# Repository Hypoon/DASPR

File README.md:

Directory Descriptions:
* 2012 - latest EAGLE project files, including schematics, boards, and libraries.
* datasheets - datasheets for all external components used in the project.

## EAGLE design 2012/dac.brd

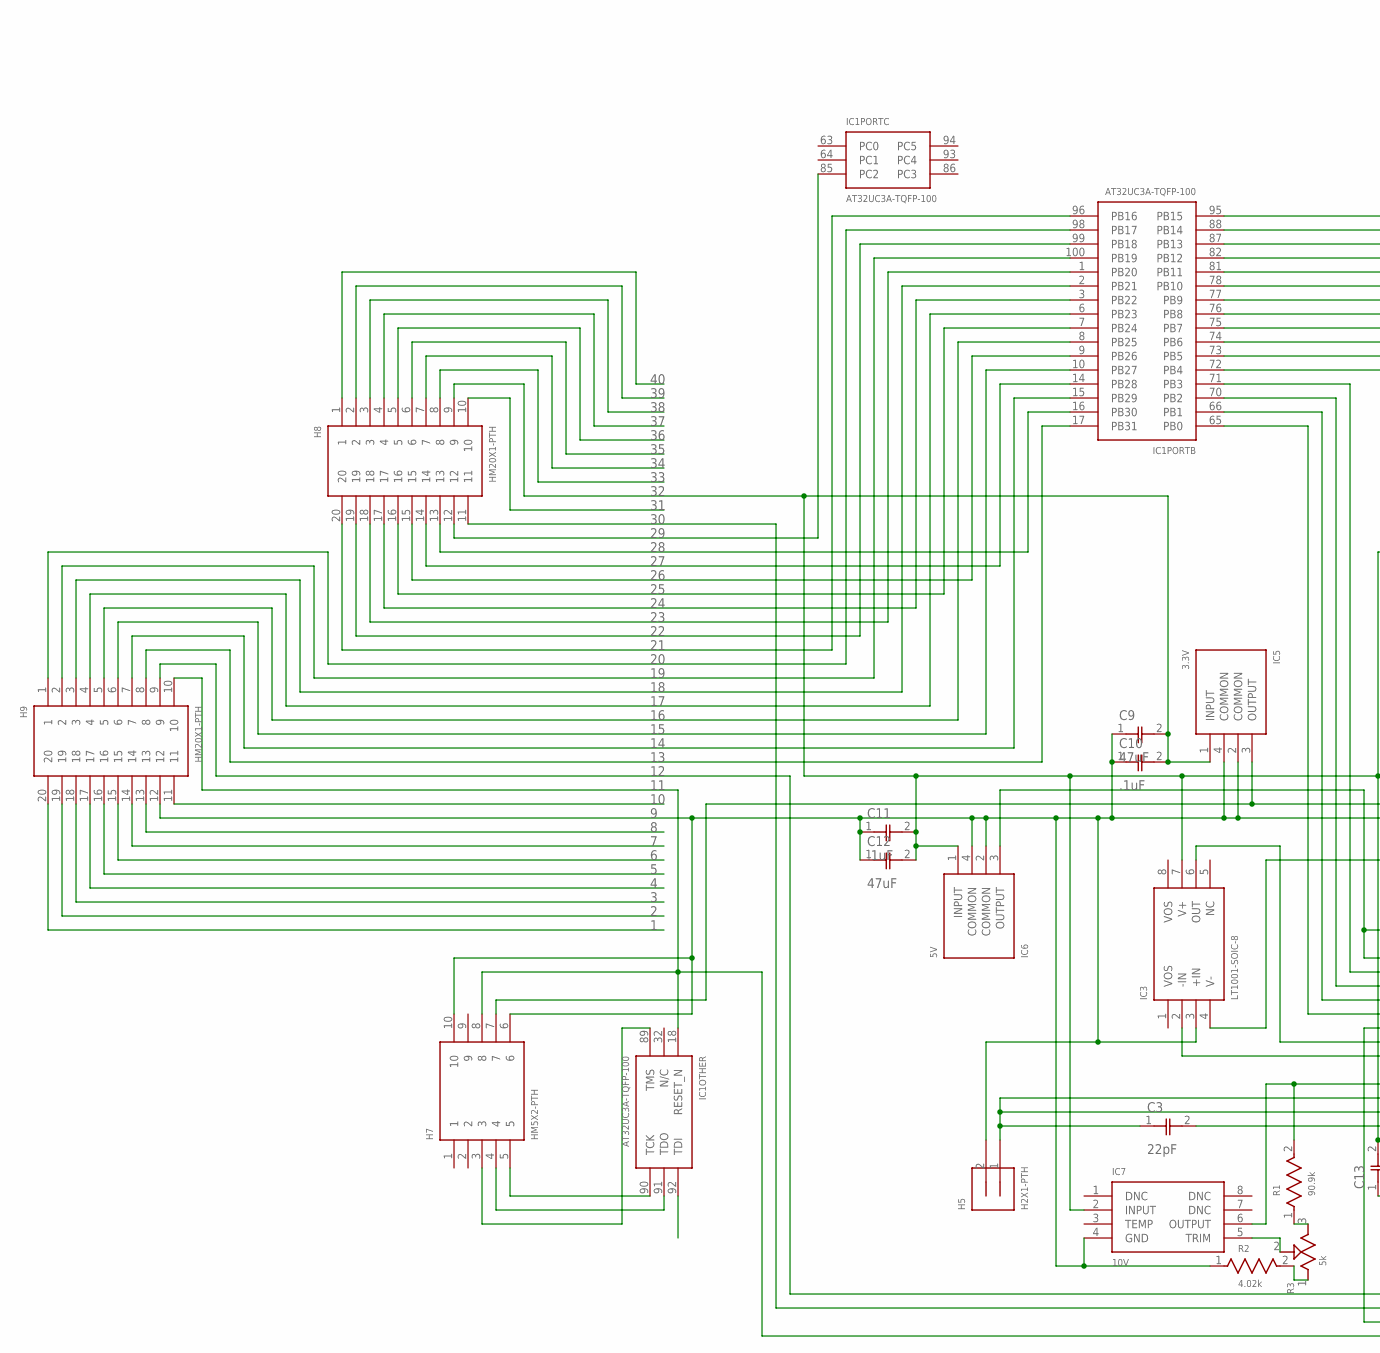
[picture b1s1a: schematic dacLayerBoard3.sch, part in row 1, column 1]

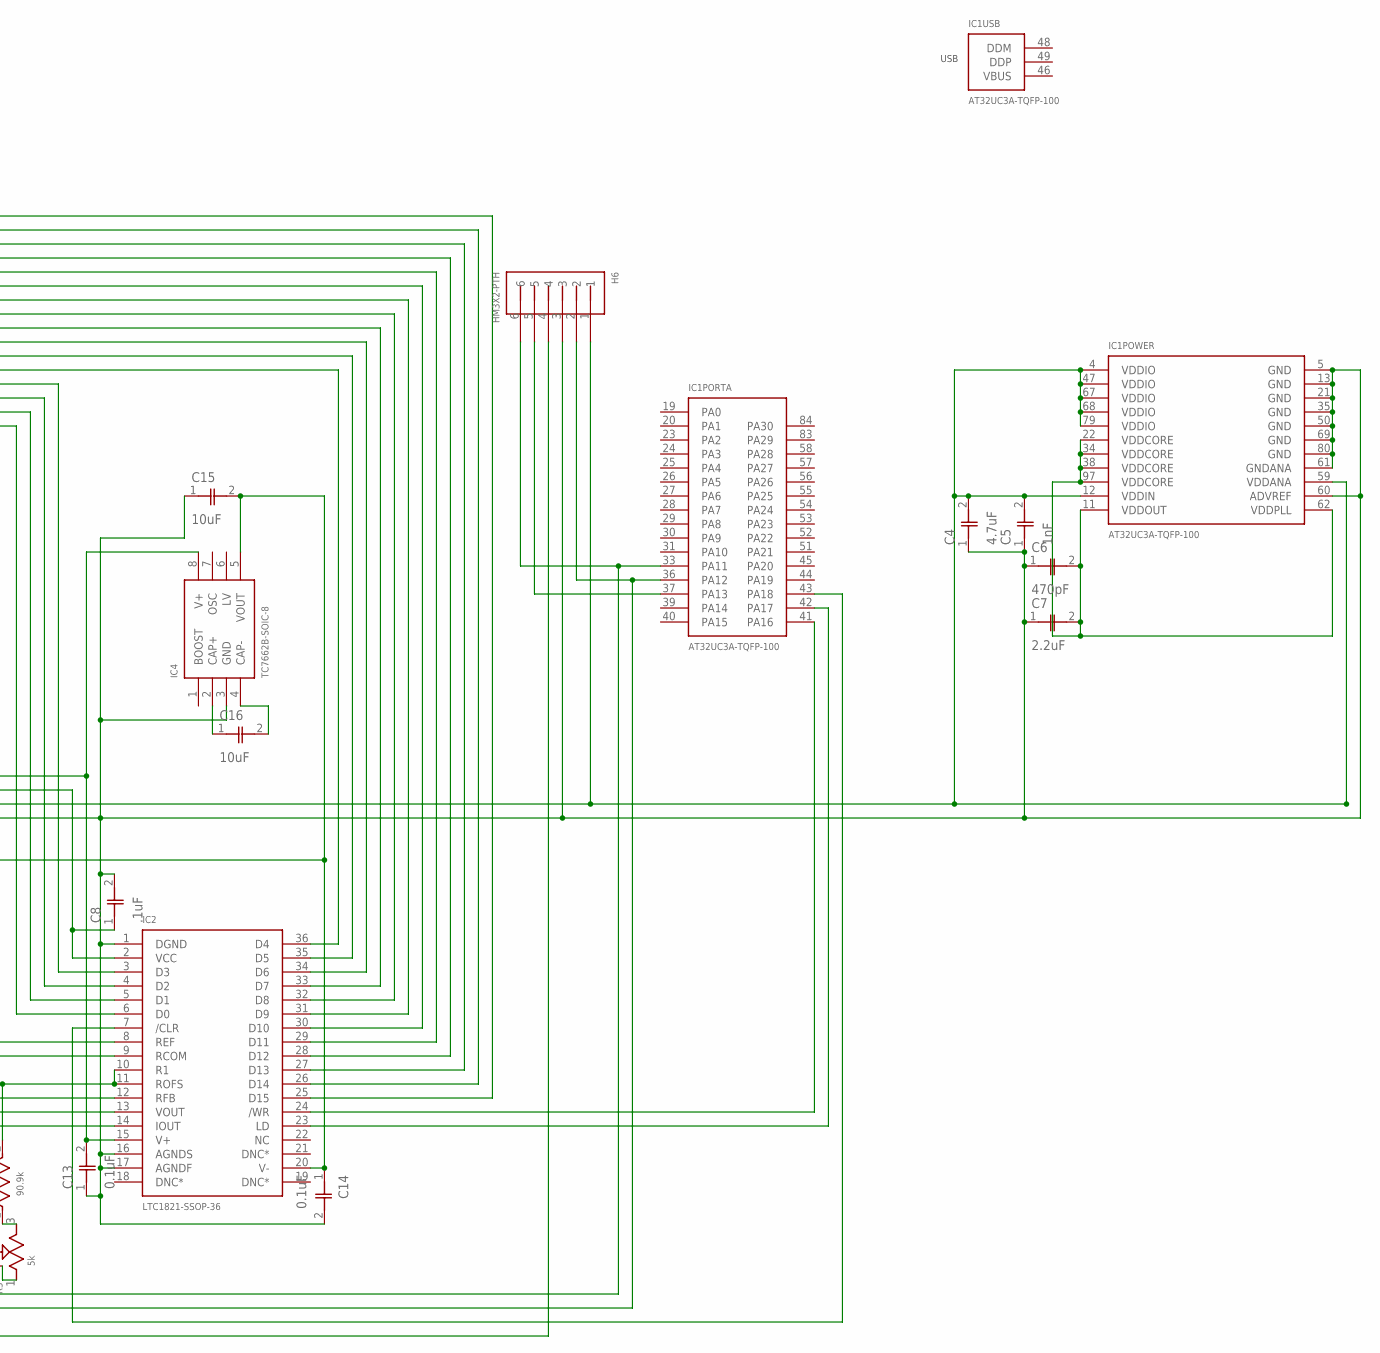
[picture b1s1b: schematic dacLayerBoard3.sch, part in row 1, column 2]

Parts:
C3: 22pF; CAP-0603
C4: 4.7uF; CAP-0603
C5: 1nF; CAP-0603
C6: 470pF; CAP-0603
C7: 2.2uF; CAP-0603
C8, C10, C11: .1uF; CAP-0603
C9, C12: 47uF; CAP-0603
C13, C14: 0.1uF; CAP-0603
C15, C16: 10uF; 0805
H5: H2X1-PTH; HM2X1-PTH
H6: HM3X2-PTH
H7: HM5X2-PTH
H8, H9: HM20X1-PTH
IC1: AT32UC3A-TQFP-100; TQFP-100
IC2: LTC1821-SSOP-36; SSOP-36
IC3: LT1001-SOIC-8; SOIC-8
IC4: TC7662B-SOIC-8; SOIC-8
IC5: 3.3V; SOT-223-4
IC6: 5V; SOT-223-4
IC7: 10V; SOIC-8
R1: 90.9k; RES-0603
R2: 4.02k; RES-0603
R3: 5k; 3303W

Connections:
1: H9.20
2: H9.19
3: H9.18
4: H9.17
5: H9.16
6: H9.15
7: H9.14
8: H9.13
9: C4.1, C5.1, C6.1, C7.1, C8.2, C9.1, C10.1, C11.1, C12.1, C13.1, C14.2, C15.1, H5.2, H6.3, H7.6, H7.10, H9.12, IC1.5 (GND), IC1.13 (GND), IC1.21 (GND), IC1.35 (GND), IC1.50 (GND), IC1.60 (ADVREF), IC1.61 (GNDANA), IC1.69 (GND), IC1.80 (GND), IC2.1 (DGND), IC2.16 (AGNDS), IC2.17 (AGNDF), IC3.3 (+IN), IC4.3 (GND), IC5.2 (COMMON), IC5.4 (COMMON), IC6.2 (COMMON), IC6.4 (COMMON), IC7.4 (GND), R2.1
10: H9.11
11: H6.4, H7.8, H9.10, IC1.18 (RESET_N)
12: H6.6, H9.9, IC1.33 (PA11)
13: H9.8, IC1.17 (PB31)
14: H9.7, IC1.15 (PB29)
15: H9.6, IC1.10 (PB27)
16: H9.5, IC1.8 (PB25)
17: H9.4, IC1.6 (PB23)
18: H9.3, IC1.2 (PB21)
19: H9.2, IC1.100 (PB19)
20: H9.1, IC1.98 (PB17)
21: H8.20, IC1.96 (PB16)
22: H8.19, IC1.99 (PB18)
23: H8.18, IC1.1 (PB20)
24: H8.17, IC1.3 (PB22)
25: H8.16, IC1.7 (PB24)
26: H8.15, IC1.9 (PB26)
27: H8.14, IC1.14 (PB28)
28: H8.13, IC1.16 (PB30)
29: H8.12, IC1.85 (PC2)
30: H6.2, H8.11, IC1.36 (PA12)
31: H8.10
32: C9.2, C10.2, C11.2, C12.2, C13.2, H8.9, IC2.15 (V+), IC3.7 (V+), IC4.8 (V+), IC5.1 (INPUT), IC6.1 (INPUT), IC7.2 (INPUT)
33: H8.8
34: H8.7
35: H8.6
36: H8.5
37: H8.4
38: H8.3
39: H8.2
40: H8.1
unnamed: IC2.9 (RCOM), IC3.2 (-IN)
unnamed: C8.1, IC2.2 (VCC), IC6.3 (OUTPUT)
unnamed: IC2.8 (REF), IC3.6 (OUT)
unnamed: C3.1, H5.1, IC2.12 (RFB), IC2.13 (VOUT)
unnamed: C3.2, IC2.14 (IOUT)
unnamed: C16.1, IC4.2 (CAP+)
unnamed: C16.2, IC4.4 (CAP-)
unnamed: C4.2, C5.2, H6.1, H7.7, IC1.4 (VDDIO), IC1.12 (VDDIN), IC1.47 (VDDIO), IC1.59 (VDDANA), IC1.67 (VDDIO), IC1.68 (VDDIO), IC1.79 (VDDIO), IC5.3 (OUTPUT)
unnamed: C6.2, C7.2, IC1.11 (VDDOUT), IC1.22 (VDDCORE), IC1.34 (VDDCORE), IC1.38 (VDDCORE), IC1.62 (VDDPLL), IC1.97 (VDDCORE)
unnamed: C14.1, C15.2, IC2.20 (V-), IC3.4 (V-), IC4.5 (VOUT)
unnamed: IC1.65 (PB0), IC2.6 (D0)
unnamed: IC1.66 (PB1), IC2.5 (D1)
unnamed: IC1.70 (PB2), IC2.4 (D2)
unnamed: IC1.71 (PB3), IC2.3 (D3)
unnamed: IC1.72 (PB4), IC2.36 (D4)
unnamed: IC1.73 (PB5), IC2.35 (D5)
unnamed: IC1.74 (PB6), IC2.34 (D6)
unnamed: IC1.75 (PB7), IC2.33 (D7)
unnamed: IC1.76 (PB8), IC2.32 (D8)
unnamed: IC1.77 (PB9), IC2.31 (D9)
unnamed: IC1.78 (PB10), IC2.30 (D10)
unnamed: IC1.81 (PB11), IC2.29 (D11)
unnamed: IC1.82 (PB12), IC2.28 (D12)
unnamed: IC1.87 (PB13), IC2.27 (D13)
unnamed: IC1.88 (PB14), IC2.26 (D14)
unnamed: IC1.95 (PB15), IC2.25 (D15)
unnamed: IC1.41 (PA16), IC2.24 (/WR)
unnamed: IC1.42 (PA17), IC2.23 (LD)
unnamed: IC1.43 (PA18), IC2.7 (/CLR)
unnamed: IC2.10 (R1), IC2.11 (ROFS), IC7.6 (OUTPUT), R1.2
unnamed: IC7.5 (TRIM), R3.2
unnamed: R1.1, R3.3
unnamed: R2.2, R3.1
unnamed: H7.5, IC1.90 (TCK)
unnamed: H7.4, IC1.91 (TDO)
unnamed: H7.3, IC1.89 (TMS)
unnamed: H6.5, IC1.37 (PA13)

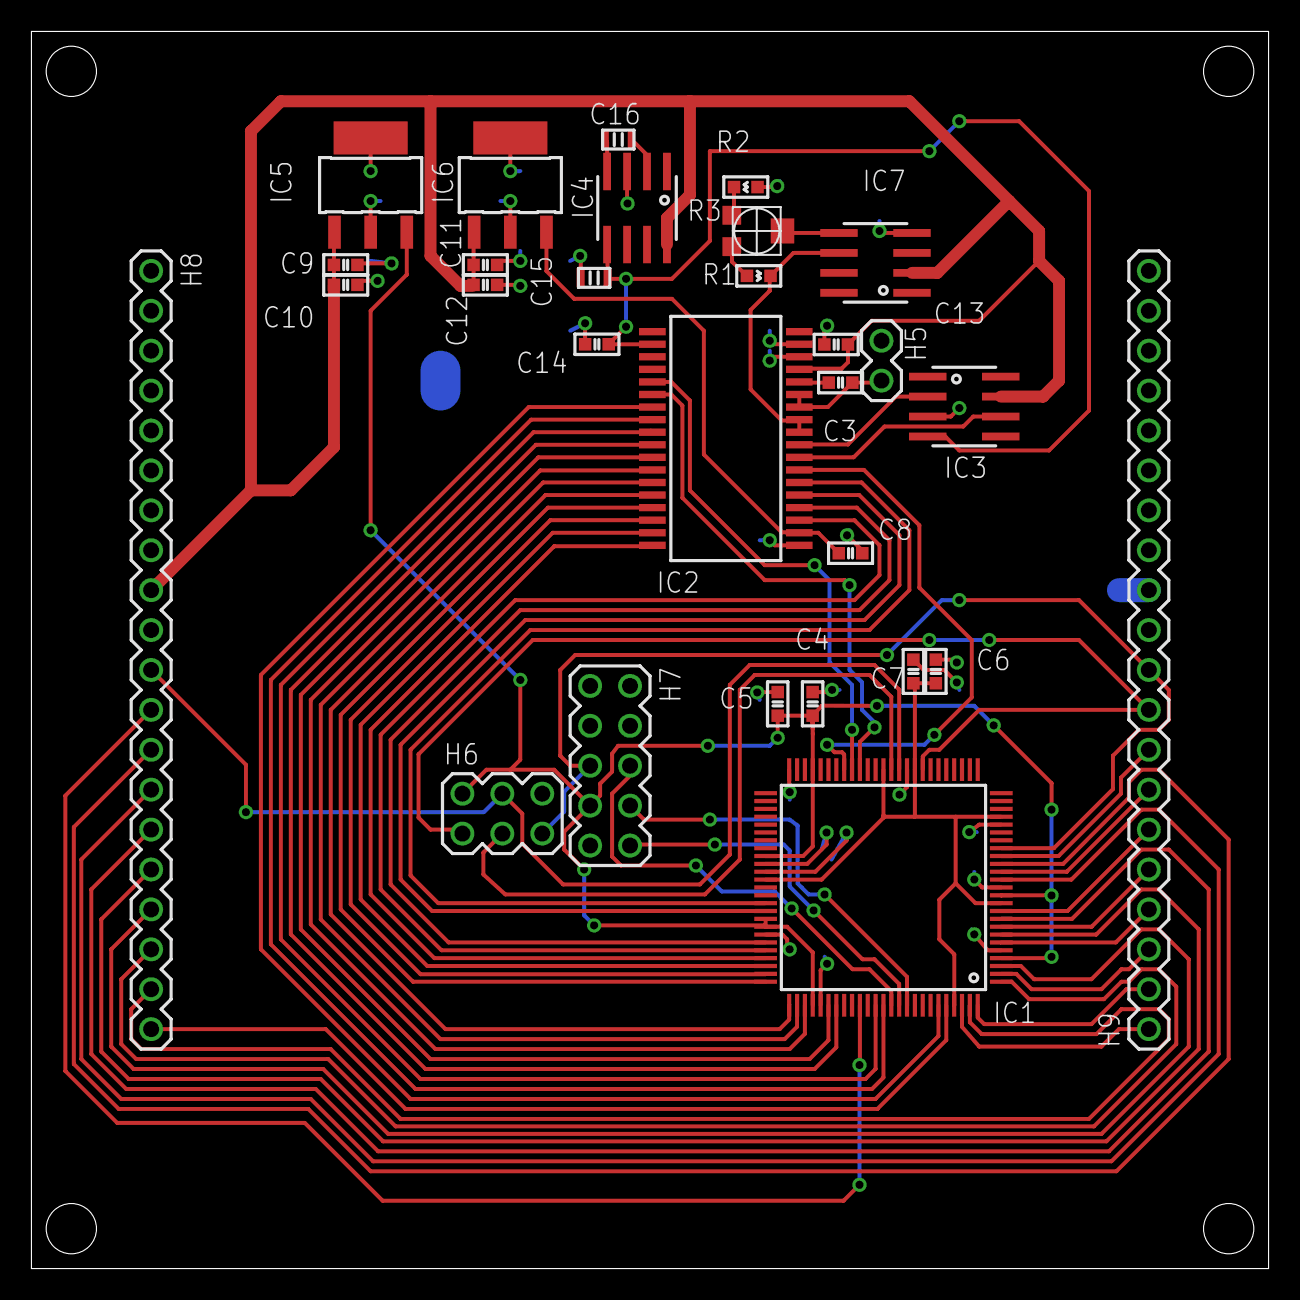
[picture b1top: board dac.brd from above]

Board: 2 copper layers, 78.7 x 78.7 mm, 29 parts (0 on the bottom side), 59 nets.

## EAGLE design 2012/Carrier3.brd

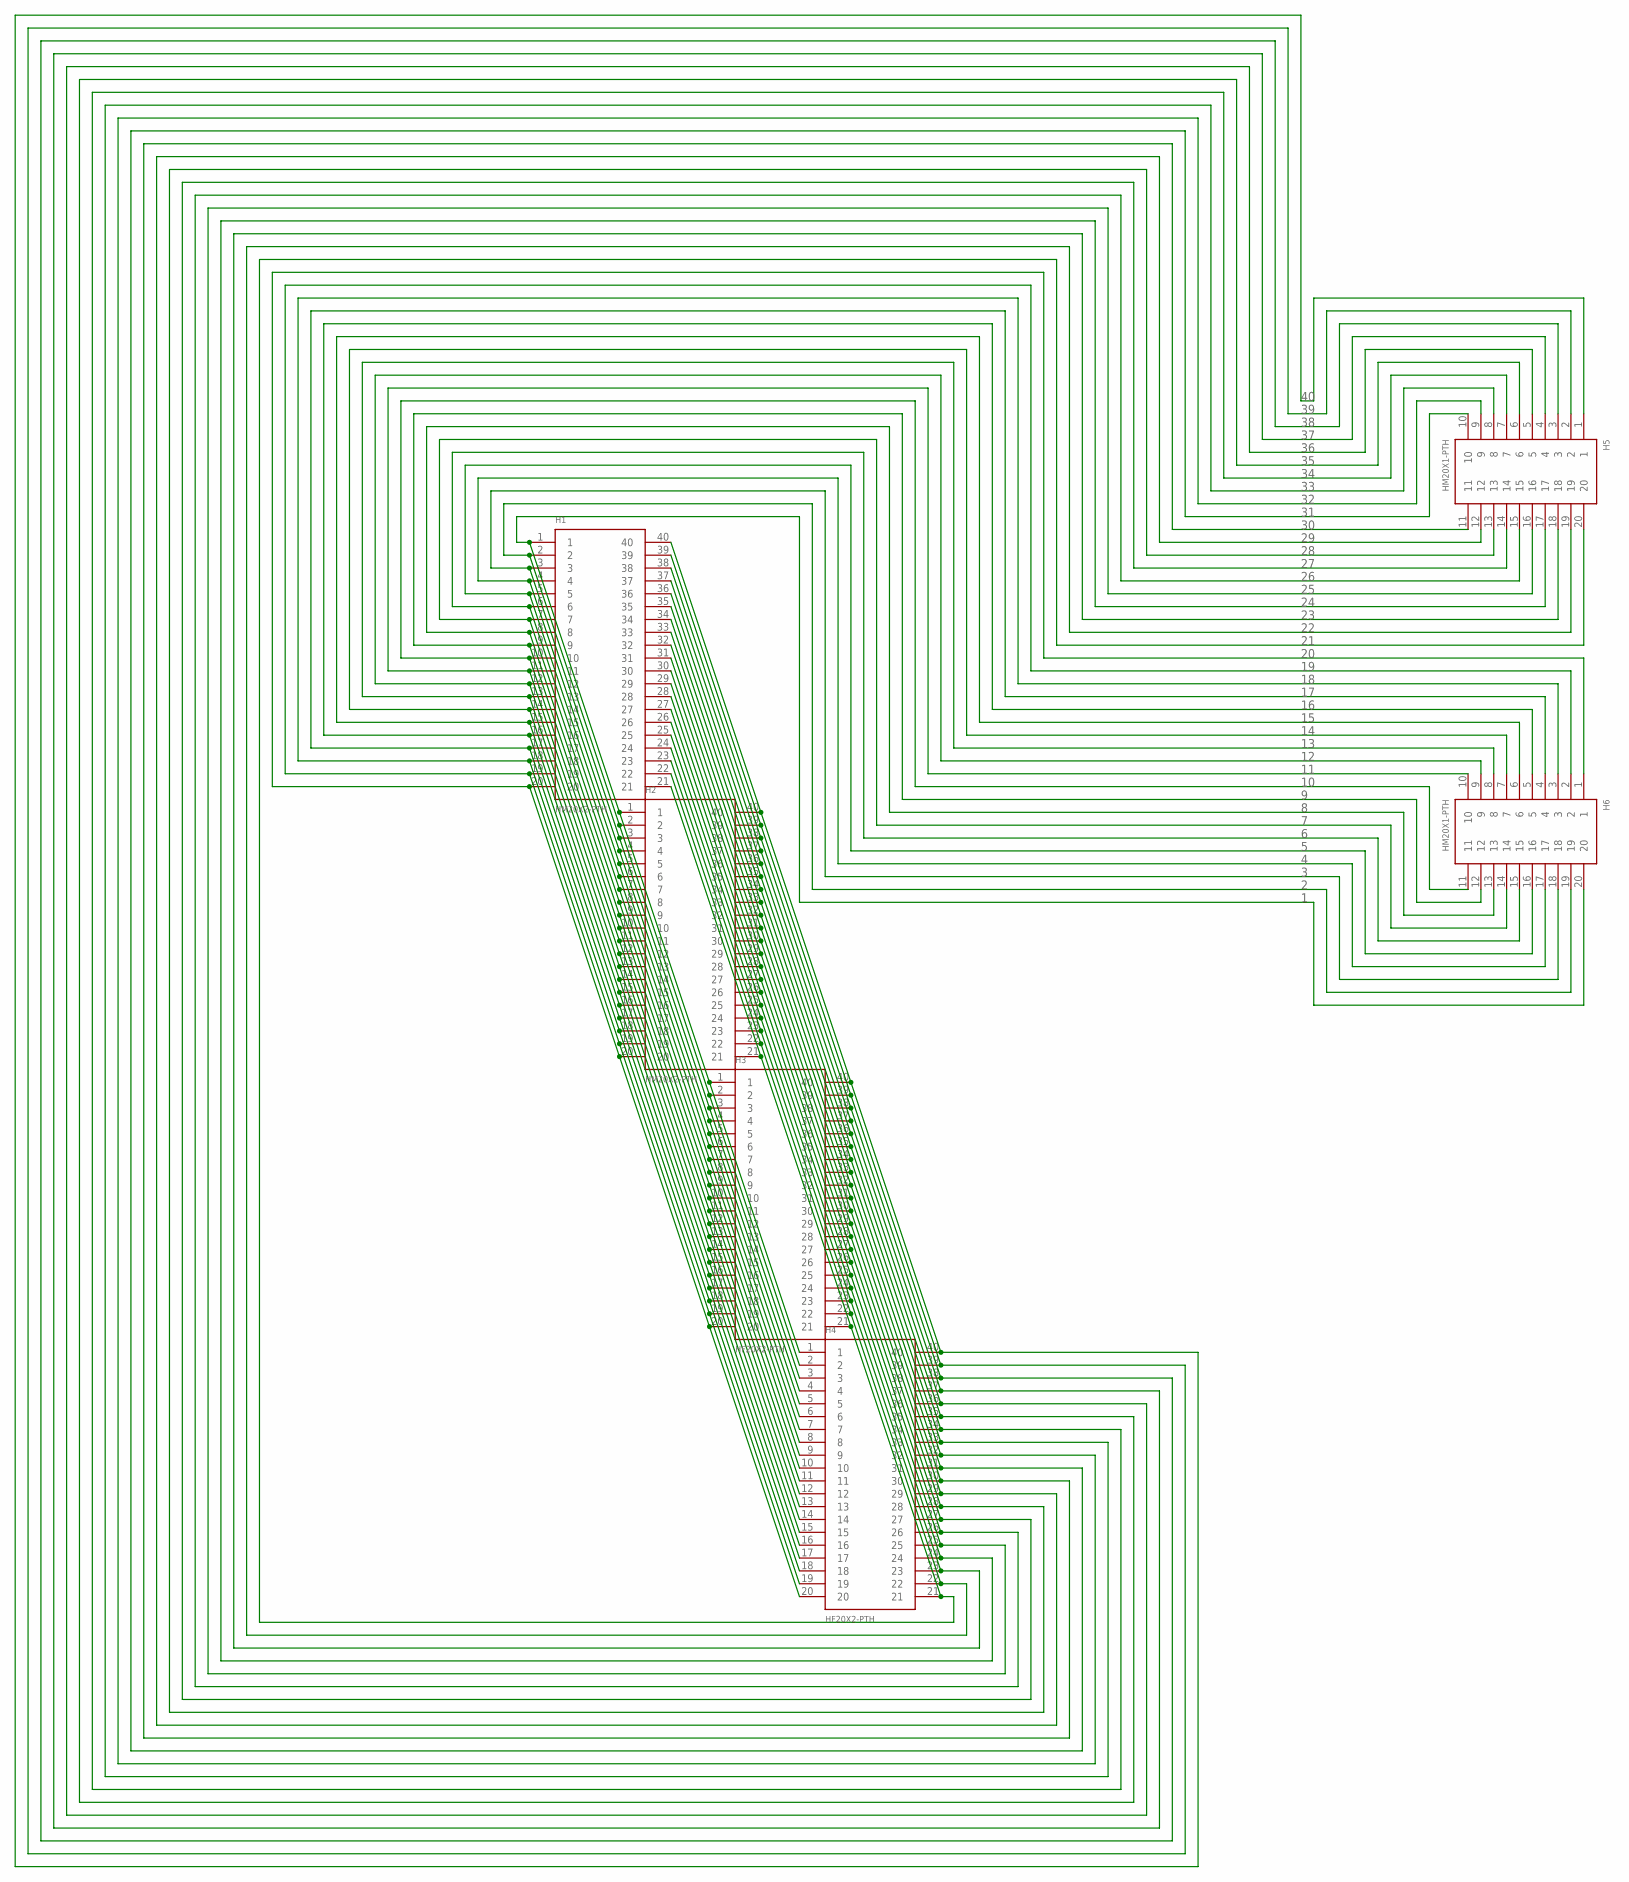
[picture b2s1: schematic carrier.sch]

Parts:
H1, H2: HM20X2-PTH
H3, H4: HF20X2-PTH
H5, H6: HM20X1-PTH

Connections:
1: H1.1, H2.1, H3.1, H4.1, H6.20
2: H1.2, H2.2, H3.2, H4.2, H6.19
3: H1.3, H2.3, H3.3, H4.3, H6.18
4: H1.4, H2.4, H3.4, H4.4, H6.17
5: H1.5, H2.5, H3.5, H4.5, H6.16
6: H1.6, H2.6, H3.6, H4.6, H6.15
7: H1.7, H2.7, H3.7, H4.7, H6.14
8: H1.8, H2.8, H3.8, H4.8, H6.13
9: H1.9, H2.9, H3.9, H4.9, H6.12
10: H1.10, H2.10, H3.10, H4.10, H6.11
11: H1.11, H2.11, H3.11, H4.11, H6.10
12: H1.12, H2.12, H3.12, H4.12, H6.9
13: H1.13, H2.13, H3.13, H4.13, H6.8
14: H1.14, H2.14, H3.14, H4.14, H6.7
15: H1.15, H2.15, H3.15, H4.15, H6.6
16: H1.16, H2.16, H3.16, H4.16, H6.5
17: H1.17, H2.17, H3.17, H4.17, H6.4
18: H1.18, H2.18, H3.18, H4.18, H6.3
19: H1.19, H2.19, H3.19, H4.19, H6.2
20: H1.20, H2.20, H3.20, H4.20, H6.1
21: H1.21, H2.21, H3.21, H4.21, H5.20
22: H1.22, H2.22, H3.22, H4.22, H5.19
23: H1.23, H2.23, H3.23, H4.23, H5.18
24: H1.24, H2.24, H3.24, H4.24, H5.17
25: H1.25, H2.25, H3.25, H4.25, H5.16
26: H1.26, H2.26, H3.26, H4.26, H5.15
27: H1.27, H2.27, H3.27, H4.27, H5.14
28: H1.28, H2.28, H3.28, H4.28, H5.13
29: H1.29, H2.29, H3.29, H4.29, H5.12
30: H1.30, H2.30, H3.30, H4.30, H5.11
31: H1.31, H2.31, H3.31, H4.31, H5.10
32: H1.32, H2.32, H3.32, H4.32, H5.9
33: H1.33, H2.33, H3.33, H4.33, H5.8
34: H1.34, H2.34, H3.34, H4.34, H5.7
35: H1.35, H2.35, H3.35, H4.35, H5.6
36: H1.36, H2.36, H3.36, H4.36, H5.5
37: H1.37, H2.37, H3.37, H4.37, H5.4
38: H1.38, H2.38, H3.38, H4.38, H5.3
39: H1.39, H2.39, H3.39, H4.39, H5.2
40: H1.40, H2.40, H3.40, H4.40, H5.1

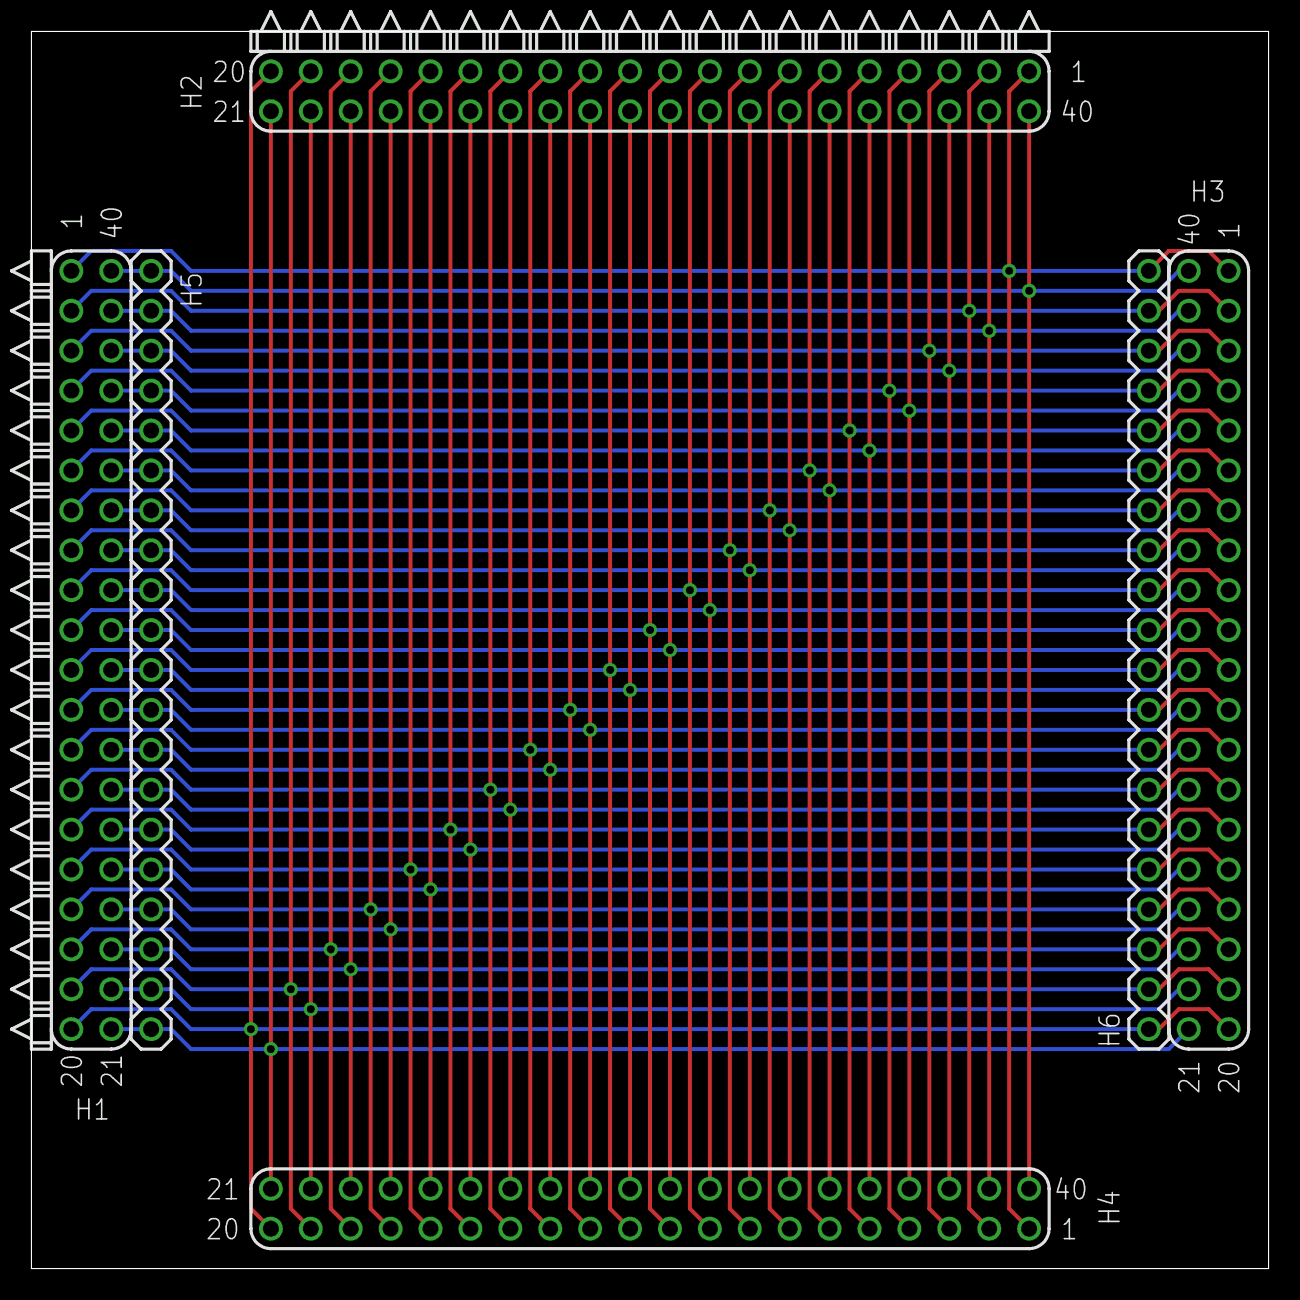
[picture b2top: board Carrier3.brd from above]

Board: 2 copper layers, 78.7 x 78.7 mm, 6 parts (0 on the bottom side), 40 nets.

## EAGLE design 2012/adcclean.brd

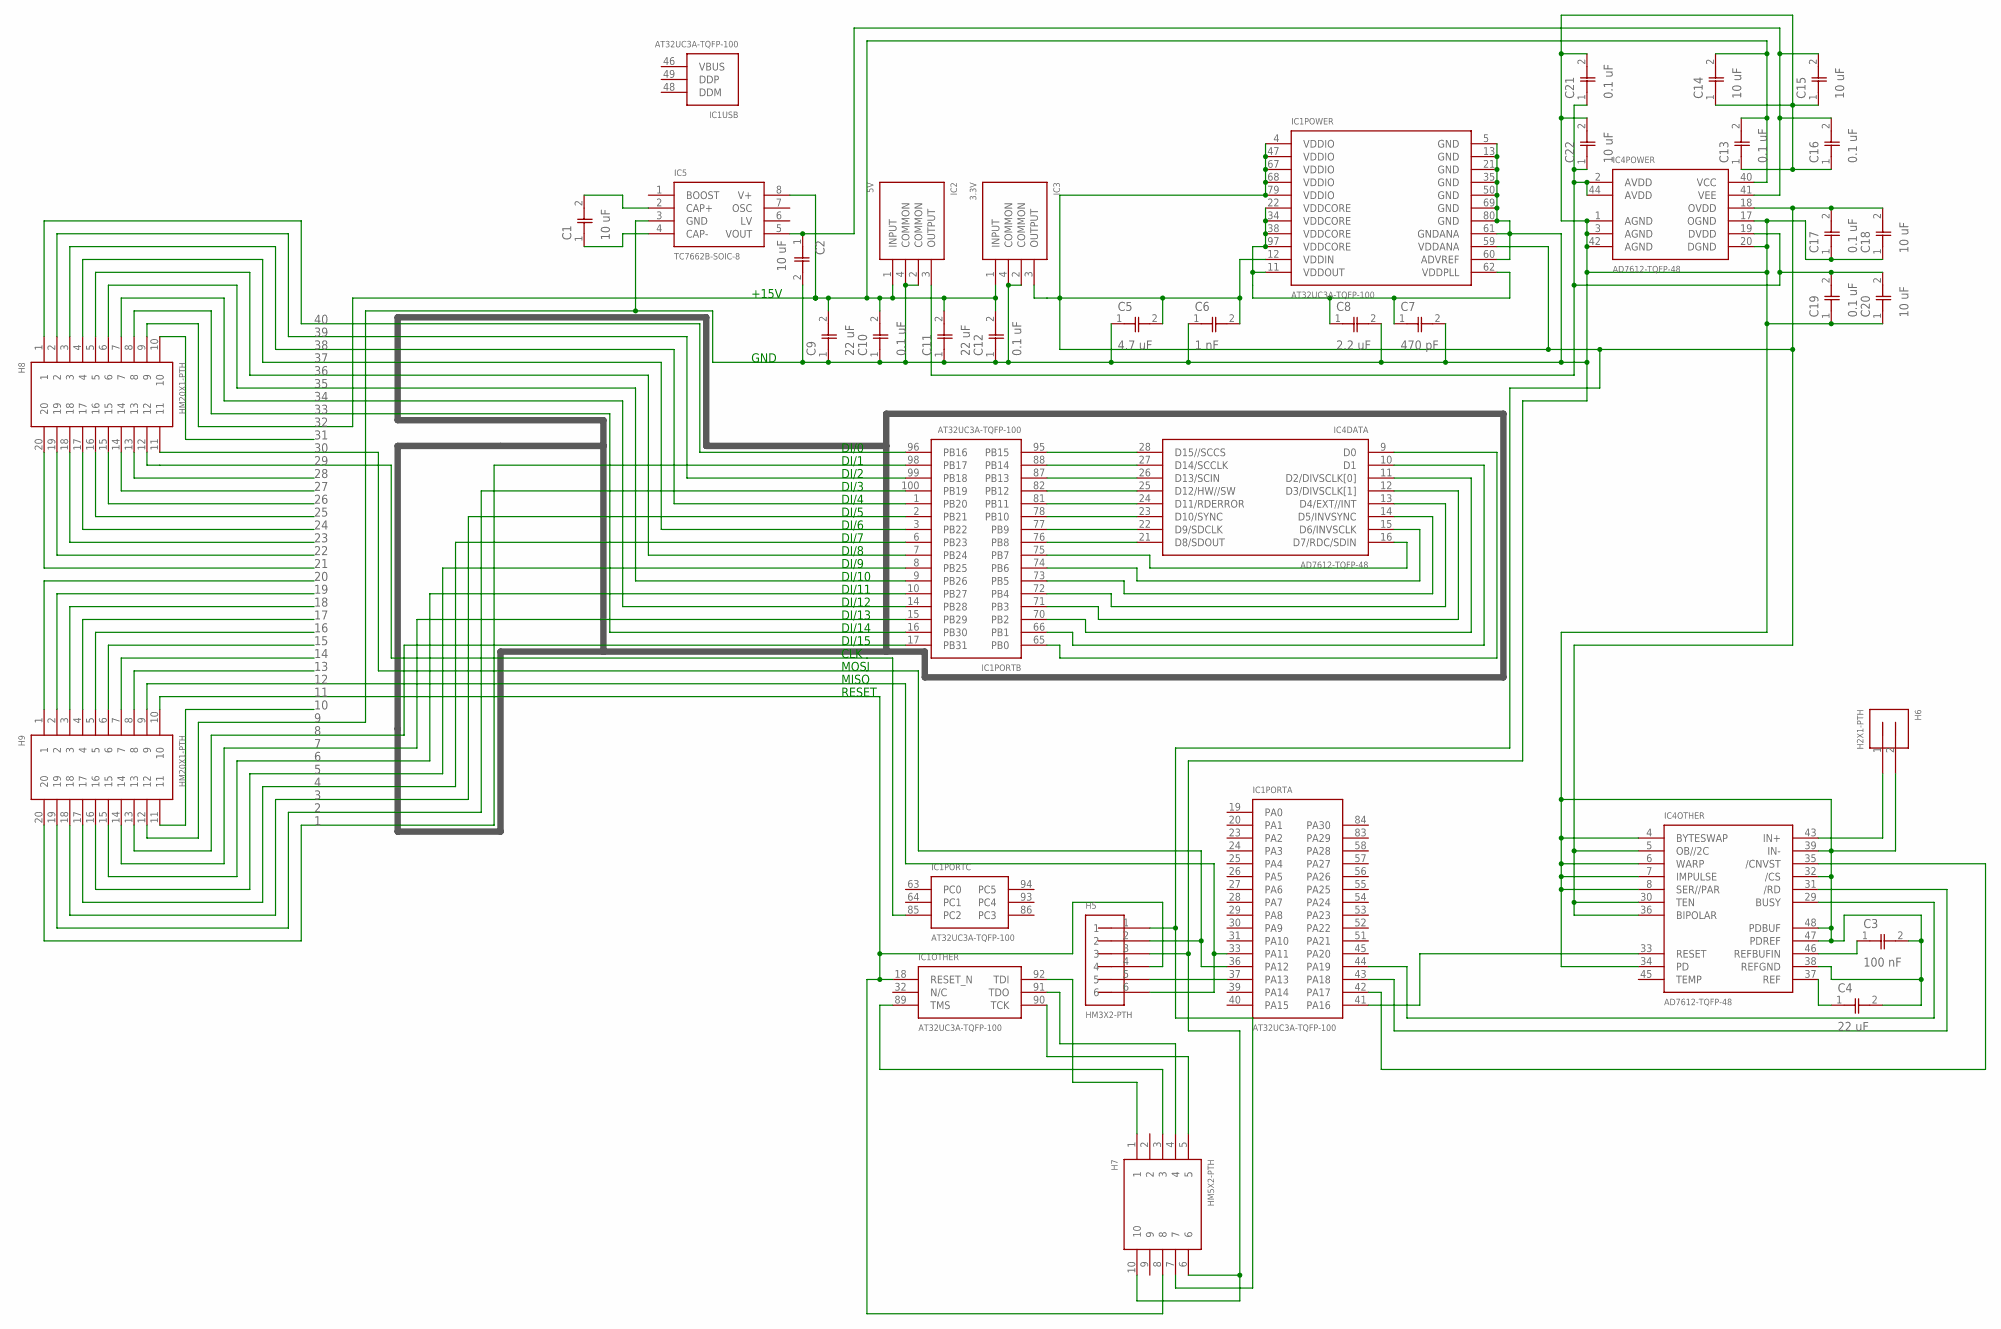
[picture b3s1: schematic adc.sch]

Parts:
C1, C2, C14, C15: 10 uF; CAP-0805
C3: 100 nF; CAP-0603
C4, C9, C11: 22 uF; CAP-0805
C5: 4.7 uF; CAP-0603
C6: 1 nF; CAP-0603
C7: 470 pF; CAP-0603
C8: 2.2 uF; CAP-0603
C10, C12, C13, C16, C17, C19, C21: 0.1 uF; CAP-0603
C18, C20, C22: 10 uF; CAP-0603
H5: HM3X2-PTH
H6: H2X1-PTH; HM2X1-PTH
H7: HM5X2-PTH
H8, H9: HM20X1-PTH
IC1: AT32UC3A-TQFP-100; TQFP-100
IC2: 5V; SOT-223-4
IC3: 3.3V; SOT-223-4
IC4: AD7612-TQFP-48; LQFP-48
IC5: TC7662B-SOIC-8; SOIC-8

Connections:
1: H9.20, IC1.98 (PB17)
1.8V: C7.1, C8.1, IC1.11 (VDDOUT), IC1.22 (VDDCORE), IC1.34 (VDDCORE), IC1.38 (VDDCORE), IC1.62 (VDDPLL), IC1.97 (VDDCORE)
2: H9.19, IC1.100 (PB19)
3: H9.18, IC1.2 (PB21)
3.3V: C5.2, C6.2, C17.2, C18.2, H5.1, H7.7, IC1.4 (VDDIO), IC1.12 (VDDIN), IC1.47 (VDDIO), IC1.59 (VDDANA), IC1.67 (VDDIO), IC1.68 (VDDIO), IC1.79 (VDDIO), IC3.3 (OUTPUT), IC4.5 (OB//2C), IC4.18 (OVDD), IC4.30 (TEN), IC4.36 (BIPOLAR)
4: H9.17, IC1.6 (PB23)
5: H9.16, IC1.8 (PB25)
5V: C19.2, C20.2, C21.1, C22.1, IC2.3 (OUTPUT), IC4.2 (AVDD), IC4.19 (DVDD), IC4.44 (AVDD)
6: H9.15, IC1.10 (PB27)
7: H9.14, IC1.15 (PB29)
8: H9.13, IC1.17 (PB31)
9: C2.2, C3.2, C4.2, C5.1, C6.1, C7.2, C8.2, C9.1, C10.1, C11.1, C12.1, C13.1, C14.1, C15.1, C16.1, C17.1, C18.1, C19.1, C20.1, C21.2, C22.2, H5.3, H6.2, H7.6, H7.10, H9.12, IC1.5 (GND), IC1.13 (GND), IC1.21 (GND), IC1.35 (GND), IC1.50 (GND), IC1.60 (ADVREF), IC1.61 (GNDANA), IC1.69 (GND), IC1.80 (GND), IC2.2 (COMMON), IC2.4 (COMMON), IC3.2 (COMMON), IC3.4 (COMMON), IC4.1 (AGND), IC4.3 (AGND), IC4.4 (BYTESWAP), IC4.6 (WARP), IC4.7 (IMPULSE), IC4.8 (SER//PAR), IC4.17 (OGND), IC4.20 (DGND), IC4.32 (/CS), IC4.34 (PD), IC4.38 (REFGND), IC4.39 (IN-), IC4.42 (AGND), IC4.47 (PDREF), IC4.48 (PDBUF), IC5.3 (GND)
10: H9.11
11: H5.4, H7.8, H9.10, IC1.18 (RESET_N)
12: H5.6, H9.9, IC1.33 (PA11)
13: H9.8
14: H9.7
15: H9.6
16: H9.5
17: H9.4
18: H9.3
19: H9.2
20: H9.1
21: H8.20
22: H8.19
23: H8.18
24: H8.17
25: H8.16
26: H8.15
27: H8.14
28: H8.13
29: H8.12, IC1.85 (PC2)
30: H5.2, H8.11, IC1.36 (PA12)
31: H8.10
32: C9.2, C10.2, C11.2, C12.2, C13.2, C14.2, H8.9, IC2.1 (INPUT), IC3.1 (INPUT), IC4.40 (VCC), IC5.8 (V+)
33: H8.8, IC1.16 (PB30)
34: H8.7, IC1.14 (PB28)
35: H8.6, IC1.9 (PB26)
36: H8.5, IC1.7 (PB24)
37: H8.4, IC1.3 (PB22)
38: H8.3, IC1.1 (PB20)
39: H8.2, IC1.99 (PB18)
40: H8.1, IC1.96 (PB16)
-15V: C2.1, C15.2, C16.2, IC4.41 (VEE), IC5.5 (VOUT)
unnamed: H5.5, IC1.37 (PA13)
unnamed: C1.2, IC5.2 (CAP+)
unnamed: IC1.65 (PB0), IC4.9 (D0)
unnamed: IC1.66 (PB1), IC4.10 (D1)
unnamed: IC1.70 (PB2), IC4.11 (D2/DIVSCLK[0])
unnamed: IC1.71 (PB3), IC4.12 (D3/DIVSCLK[1])
unnamed: C1.1, IC5.4 (CAP-)
unnamed: IC1.72 (PB4), IC4.13 (D4/EXT//INT)
unnamed: IC1.73 (PB5), IC4.14 (D5/INVSYNC)
unnamed: IC1.74 (PB6), IC4.15 (D6/INVSCLK)
unnamed: IC1.76 (PB8), IC4.21 (D8/SDOUT)
unnamed: IC1.77 (PB9), IC4.22 (D9/SDCLK)
unnamed: IC1.78 (PB10), IC4.23 (D10/SYNC)
unnamed: IC1.81 (PB11), IC4.24 (D11/RDERROR)
unnamed: IC1.82 (PB12), IC4.25 (D12/HW//SW)
unnamed: IC1.87 (PB13), IC4.26 (D13/SCIN)
unnamed: IC1.88 (PB14), IC4.27 (D14/SCCLK)
unnamed: IC1.95 (PB15), IC4.28 (D15//SCCS)
unnamed: IC1.75 (PB7), IC4.16 (D7/RDC/SDIN)
unnamed: IC1.41 (PA16), IC4.33 (RESET)
unnamed: IC1.44 (PA19), IC4.29 (BUSY)
unnamed: IC1.42 (PA17), IC4.35 (/CNVST)
unnamed: C3.1, IC4.46 (REFBUFIN)
unnamed: C4.1, IC4.37 (REF)
unnamed: IC1.43 (PA18), IC4.31 (/RD)
unnamed: H6.1, IC4.43 (IN+)
unnamed: H7.5, IC1.90 (TCK)
unnamed: H7.4, IC1.91 (TDO)
unnamed: H7.3, IC1.89 (TMS)
unnamed: H7.1, IC1.92 (TDI)

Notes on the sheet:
DI/0
DI/1
DI/2
DI/3
DI/4
DI/5
DI/6
DI/7
DI/8
DI/9
DI/10
DI/11
DI/12
DI/13
DI/14
DI/15
MISO
MOSI
CLK
RESET
+15V
GND

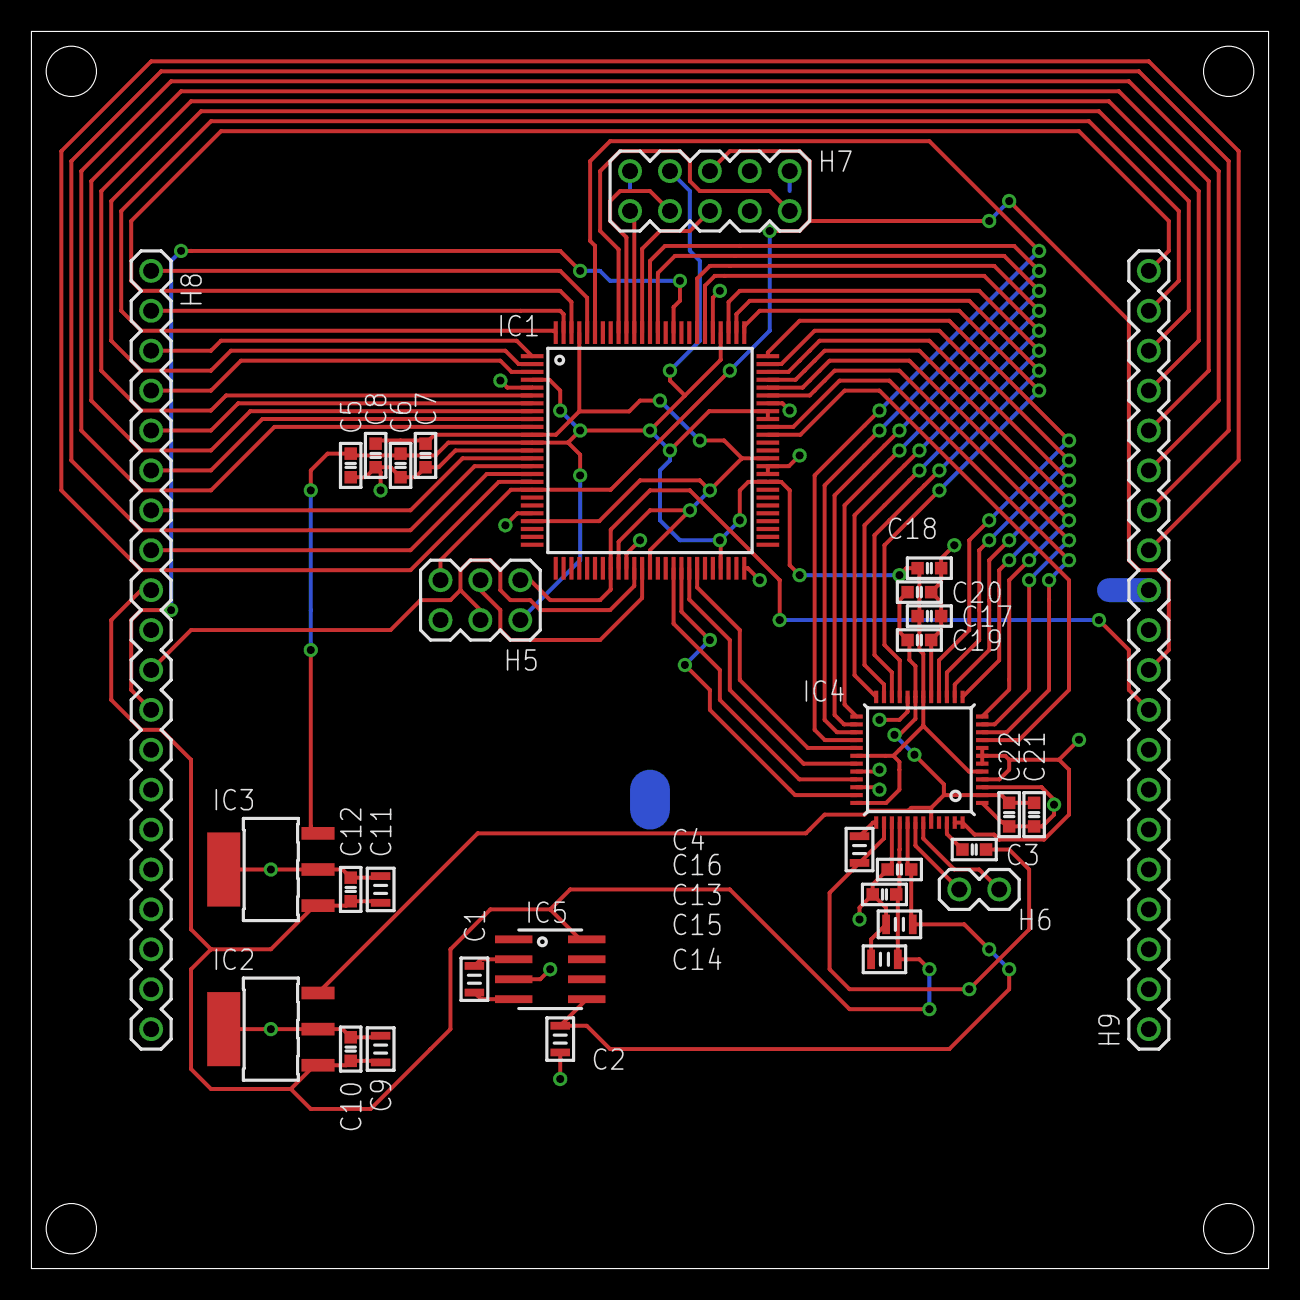
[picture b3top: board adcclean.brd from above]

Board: 2 copper layers, 78.7 x 78.7 mm, 32 parts (0 on the bottom side), 56 nets.

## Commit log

2012-01-17 second commit
2012-01-17 Just a test
2012-01-17 clear
2012-01-24 EagleFiles
2012-01-25 Datasheets
2012-01-25 Adding ADC Datasheet
2012-01-25 Added readme to root
2012-02-15 Ignore OS metadata
2012-06-28 Created root Eclipse project.
    Created and configured Eclipse project for compiling and programming
    code into Arduino Duemilanove microcontroller.
2012-07-11 Update master
2012-07-11 Fixing personal settings being stored in repo (1)
2012-07-11 Fixing more personal settings in repo (2)
2012-07-11 Fixing gitignore
2012-07-11 Fixing GitIgnore (again)
2012-07-11 Updated gitignore AGAIN AGAIN
2012-07-11 Fixing prefs again
2012-07-11 removing more personal prefs!
2012-07-11 Changed main.c so the LED blinks 10x faster.
2012-07-11 Changed 90s to 100s.
2012-07-11 change CPU speed to 20 MHz
2012-07-11 Changed led on time to 200 ms
2012-07-11 Mitch made an error; I had to fix it.
2012-07-11 testing eagle
2012-07-11 Look, I made an example board too!!!
2012-07-11 deleted unworthy files
